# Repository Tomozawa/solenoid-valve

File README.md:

# solenoid-valve
[こちら](https://github.com/funi007/solenoid-valve.git)の電磁弁基板の改良版です。未テストですので使用に際しては十分注意してください。

# 履歴
## 改良基板の初版
- 2023/11/03
- ERC and DRC check
- 6f543627d558cafed8350256de44e78604443efa
- 改良基板の初期版。未テスト。

# 改良点
## フォトリレーが焼ける問題を解消
フォトリレーに負電圧がかかることで内部のFETが焼ける問題を解消しました。フォトリレー自体を採用せず、FETによるオープンドレイン出力としました。

## XT30コネクタに変更
駆動用電源のコネクタをEPコネクタからXT30コネクタ(オス)に変更しました。

## DCDCコンバータの安定性・効率を向上
DCDCコンバータに適正な負荷をかけ、連続モードでの動作とすることで、DCDCコンバータの安定性を改善ました。また、効率の上昇や高調波ノイズの低減も期待できます。

## フォトカプラへの配線を改善
ベタパターンの島ができにくいように、フォトカプラへの配線をまとめました。

# 問題点

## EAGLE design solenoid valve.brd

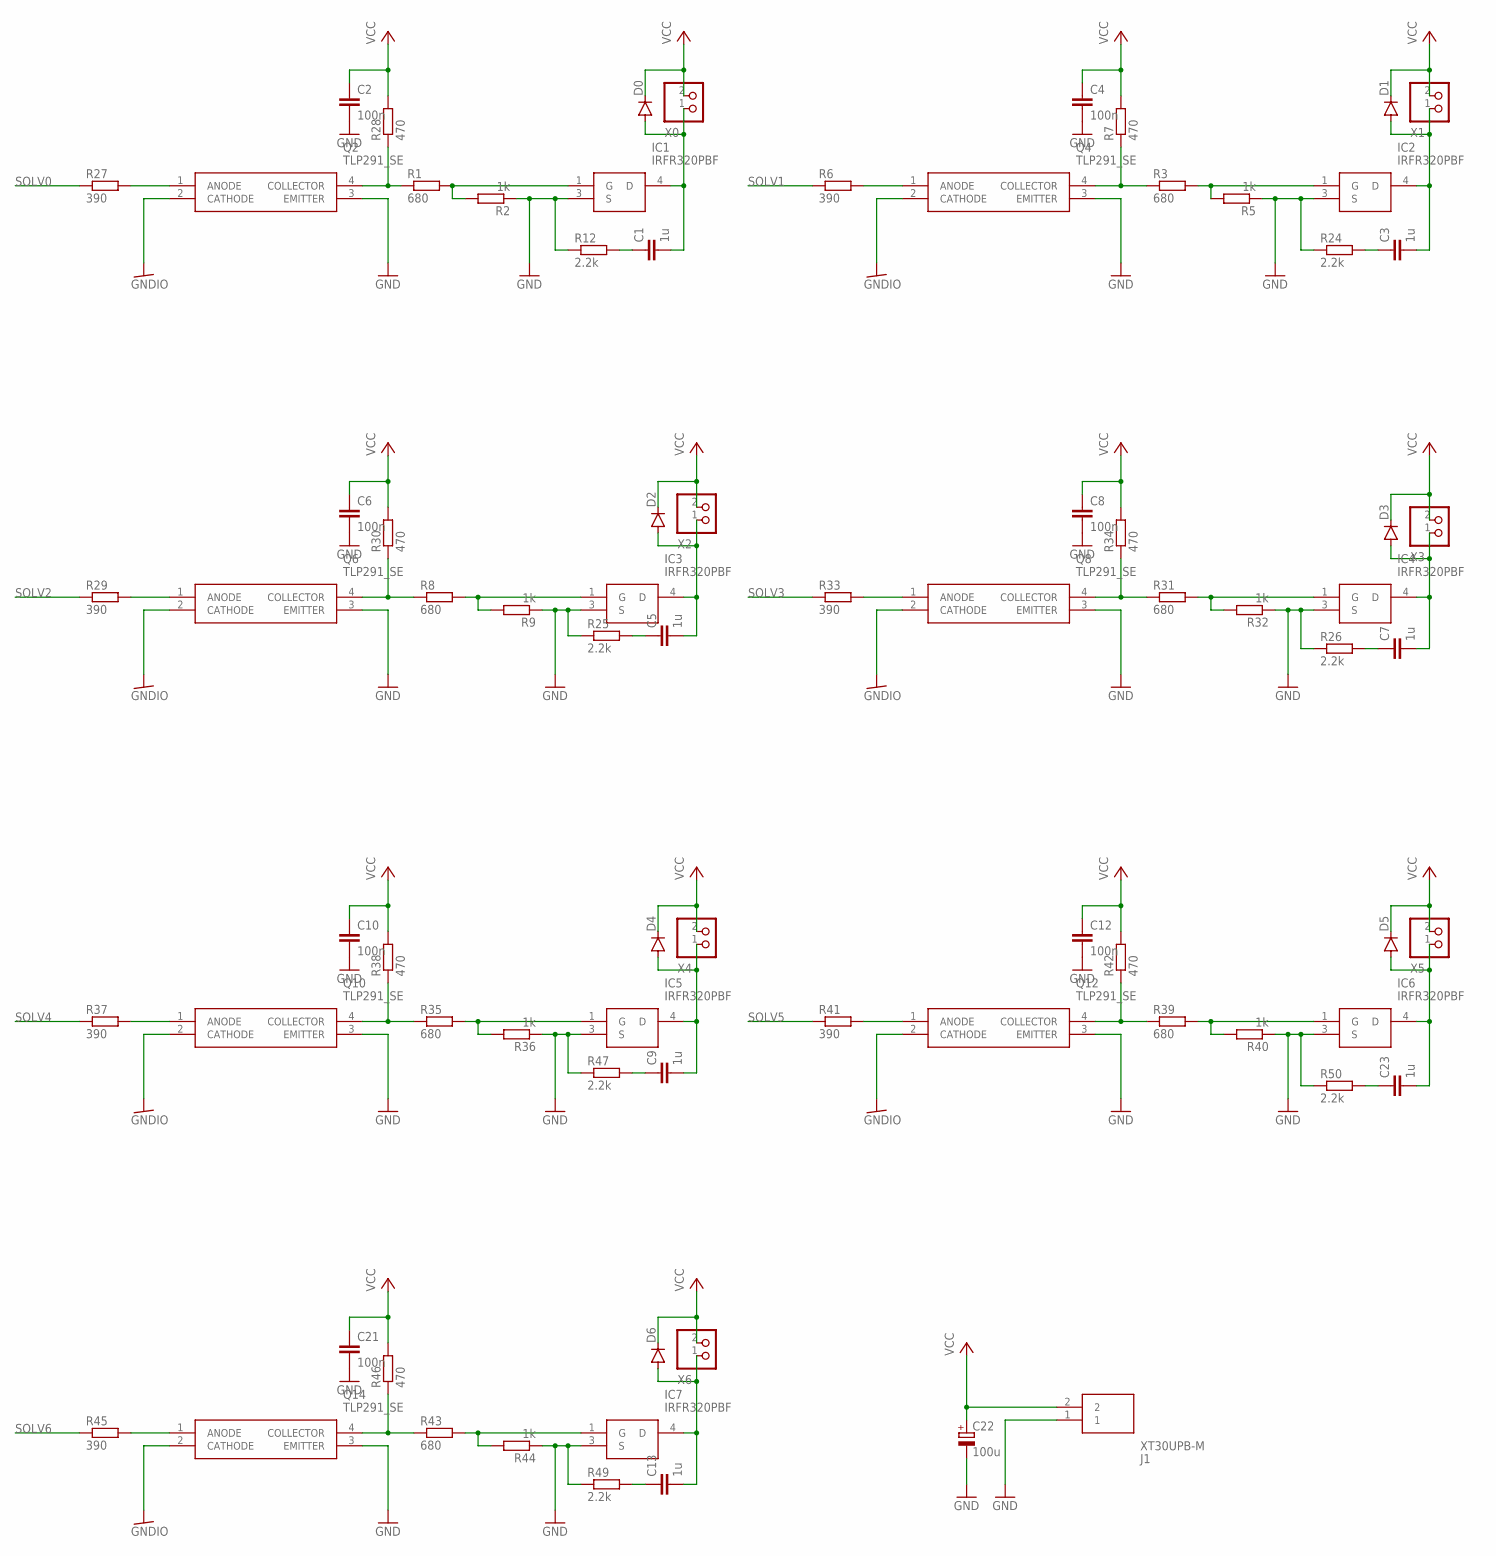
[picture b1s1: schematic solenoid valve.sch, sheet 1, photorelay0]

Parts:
C1, C3, C5, C7, C9, C13, C23: 1u; C0603
C2, C4, C6, C8, C10, C12, C21: 100n; C0603
C22: 100u; E2-5
D0, D1, D2, D3, D4, D5, D6: DIODE-SOD123; SOD123
IC1, IC2, IC3, IC4, IC5, IC6, IC7: IRFR320PBF; TO228P990X238-3N
J1: XT30UPB-M; SHDR2W160P0X500_1X2_1020X520X1
Q2, Q4, Q6, Q8, Q10, Q12, Q14: TLP291_SE; SOIC127P700X230-4N
R1, R3, R8, R31, R35, R39, R43: 680; R0603
R2, R5, R9, R32, R36, R40, R44: 1k; R0603
R6, R27, R29, R33, R37, R41, R45: 390; R0603
R7, R28, R30, R34, R38, R42, R46: 470; R0603
R12, R24, R25, R26, R47, R49, R50: 2.2k; R0603
X0, X1, X2, X3, X4, X5, X6: S2B-XASK-1

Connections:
GND: C2.2, C4.2, C6.2, C8.2, C10.2, C12.2, C21.2, C22.-, IC1.3 (S), IC2.3 (S), IC3.3 (S), IC4.3 (S), IC5.3 (S), IC6.3 (S), IC7.3 (S), J1.1, Q2.3 (EMITTER), Q4.3 (EMITTER), Q6.3 (EMITTER), Q8.3 (EMITTER), Q10.3 (EMITTER), Q12.3 (EMITTER), Q14.3 (EMITTER), R2.1, R5.1, R9.1, R12.1, R24.1, R25.1, R26.1, R32.1, R36.1, R40.1, R44.1, R47.1, R49.1, R50.1
GNDIO: Q2.2 (CATHODE), Q4.2 (CATHODE), Q6.2 (CATHODE), Q8.2 (CATHODE), Q10.2 (CATHODE), Q12.2 (CATHODE), Q14.2 (CATHODE); also elsewhere on the board
unnamed: IC2.1 (G), R3.2, R5.2
unnamed: C3.2, D1.A, IC2.4 (D), X1.1
unnamed: Q2.4 (COLLECTOR), R1.1, R28.1
unnamed: Q4.1 (ANODE), R6.2
unnamed: Q4.4 (COLLECTOR), R3.1, R7.1
unnamed: IC1.1 (G), R1.2, R2.2
unnamed: C1.2, D0.A, IC1.4 (D), X0.1
unnamed: IC3.1 (G), R8.2, R9.2
unnamed: Q2.1 (ANODE), R27.2
unnamed: C5.2, D2.A, IC3.4 (D), X2.1
unnamed: Q6.1 (ANODE), R29.2
unnamed: Q6.4 (COLLECTOR), R8.1, R30.1
unnamed: C7.2, D3.A, IC4.4 (D), X3.1
unnamed: C9.2, D4.A, IC5.4 (D), X4.1
unnamed: IC4.1 (G), R31.2, R32.2
unnamed: C3.1, R24.2
unnamed: C23.1, R50.2
unnamed: C23.2, D5.A, IC6.4 (D), X5.1
unnamed: C5.1, R25.2
unnamed: IC7.1 (G), R43.2, R44.2
unnamed: Q8.1 (ANODE), R33.2
unnamed: Q8.4 (COLLECTOR), R31.1, R34.1
unnamed: IC5.1 (G), R35.2, R36.2
unnamed: Q10.1 (ANODE), R37.2
unnamed: Q10.4 (COLLECTOR), R35.1, R38.1
unnamed: IC6.1 (G), R39.2, R40.2
unnamed: Q12.1 (ANODE), R41.2
unnamed: Q12.4 (COLLECTOR), R39.1, R42.1
unnamed: C13.2, D6.A, IC7.4 (D), X6.1
unnamed: Q14.1 (ANODE), R45.2
unnamed: Q14.4 (COLLECTOR), R43.1, R46.1
unnamed: C7.1, R26.2
unnamed: C9.1, R47.2
unnamed: C13.1, R49.2
unnamed: C1.1, R12.2
SOLV0: R27.1; also elsewhere on the board
SOLV1: R6.1; also elsewhere on the board
SOLV2: R29.1; also elsewhere on the board
SOLV3: R33.1; also elsewhere on the board
SOLV4: R37.1; also elsewhere on the board
SOLV5: R41.1; also elsewhere on the board
SOLV6: R45.1; also elsewhere on the board
VCC: C2.1, C4.1, C6.1, C8.1, C10.1, C12.1, C21.1, C22.+, D0.C, D1.C, D2.C, D3.C, D4.C, D5.C, D6.C, J1.2, R7.2, R28.2, R30.2, R34.2, R38.2, R42.2, R46.2, X0.2, X1.2, X2.2, X3.2, X4.2, X5.2, X6.2

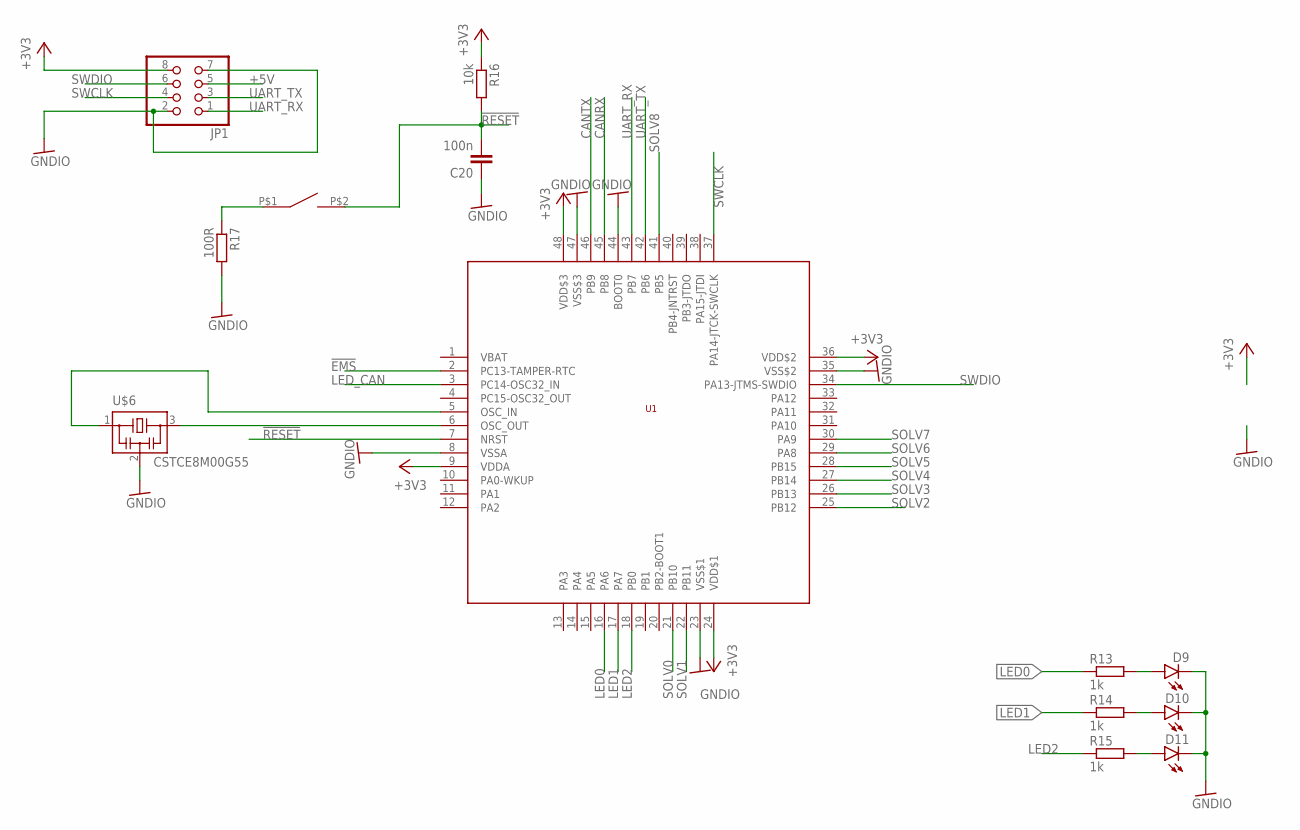
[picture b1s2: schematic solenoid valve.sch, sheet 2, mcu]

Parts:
C20: 100n; C0603
D9, D10, D11: LEDCHIPLED_0805; CHIPLED_0805
JP1: PINHD-2X4; 2X04
R13, R14, R15: 1k; R0603
R16: 10k; R0603
R17: 100R; R0603
SW1: SWITCH_TACTILETOP; SWITCH_TACTILE_3X6
U1: STM32F103C8; LQFP48
U$6: CSTCE8M00G55

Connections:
!EMS: U1.2 (PC13-TAMPER-RTC); also elsewhere on the board
!RESET: C20.2, R16.2, SW1.P$2 (2), U1.7 (NRST)
+3V3: JP1.8, R16.1, U1.9 (VDDA), U1.24 (VDD$1), U1.36 (VDD$2), U1.48 (VDD$3); also elsewhere on the board
+5V: JP1.5; also elsewhere on the board
CANRX: U1.45 (PB8); also elsewhere on the board
CANTX: U1.46 (PB9); also elsewhere on the board
GNDIO: C20.1, D9.C, D10.C, D11.C, JP1.2, JP1.7, R17.2, U1.8 (VSSA), U1.23 (VSS$1), U1.35 (VSS$2), U1.44 (BOOT0), U1.47 (VSS$3), U$6.2; also elsewhere on the board
LED0: R13.1, U1.16 (PA6)
LED1: R14.1, U1.17 (PA7)
LED2: R15.1, U1.18 (PB0)
LED_CAN: U1.3 (PC14-OSC32_IN); also elsewhere on the board
unnamed: D10.A, R14.2
unnamed: D9.A, R13.2
unnamed: U1.6 (OSC_OUT), U$6.3
unnamed: R17.1, SW1.P$1 (1)
unnamed: U1.5 (OSC_IN), U$6.1
unnamed: D11.A, R15.2
SOLV0: U1.21 (PB10); also elsewhere on the board
SOLV1: U1.22 (PB11); also elsewhere on the board
SOLV2: U1.25 (PB12); also elsewhere on the board
SOLV3: U1.26 (PB13); also elsewhere on the board
SOLV4: U1.27 (PB14); also elsewhere on the board
SOLV5: U1.28 (PB15); also elsewhere on the board
SOLV6: U1.29 (PA8); also elsewhere on the board
SOLV7: U1.30 (PA9)
SOLV8: U1.41 (PB5)
SWCLK: JP1.4, U1.37 (PA14-JTCK-SWCLK)
SWDIO: JP1.6, U1.34 (PA13-JTMS-SWDIO)
UART_RX: JP1.1, U1.43 (PB7)
UART_TX: JP1.3, U1.42 (PB6)

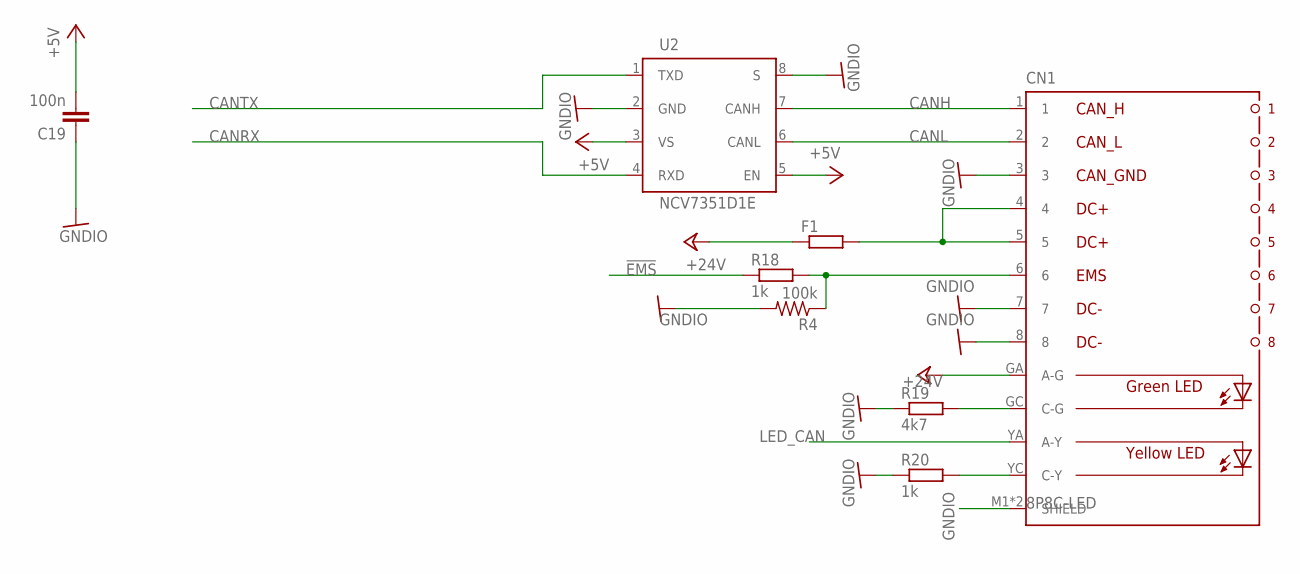
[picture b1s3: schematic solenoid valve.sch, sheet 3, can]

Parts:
C19: 100n; C0603
CN1: 8P8C-LED
F1: R-EU_R1206; R1206
R4: 100k; R0603
R18, R20: 1k; R0603
R19: 4k7; R0603
U2: NCV7351D1E; SO08

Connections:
!EMS: R18.1; also elsewhere on the board
+5V: C19.2, U2.3 (VS), U2.5 (EN); also elsewhere on the board
+24V: CN1.GA (A-G), F1.1; also elsewhere on the board
CANH: CN1.1, U2.7 (CANH)
CANL: CN1.2, U2.6 (CANL)
CANRX: U2.4 (RXD); also elsewhere on the board
CANTX: U2.1 (TXD); also elsewhere on the board
GNDIO: C19.1, CN1.3, CN1.7, CN1.8, CN1.M1 (SHIELD), CN1.M2 (SHIELD), R4.2, R19.1, R20.1, U2.2 (GND), U2.8 (S); also elsewhere on the board
LED_CAN: CN1.YA (A-Y); also elsewhere on the board
unnamed: CN1.4, CN1.5, F1.2
unnamed: CN1.YC (C-Y), R20.2
unnamed: CN1.GC (C-G), R19.2
unnamed: CN1.6, R4.1, R18.2

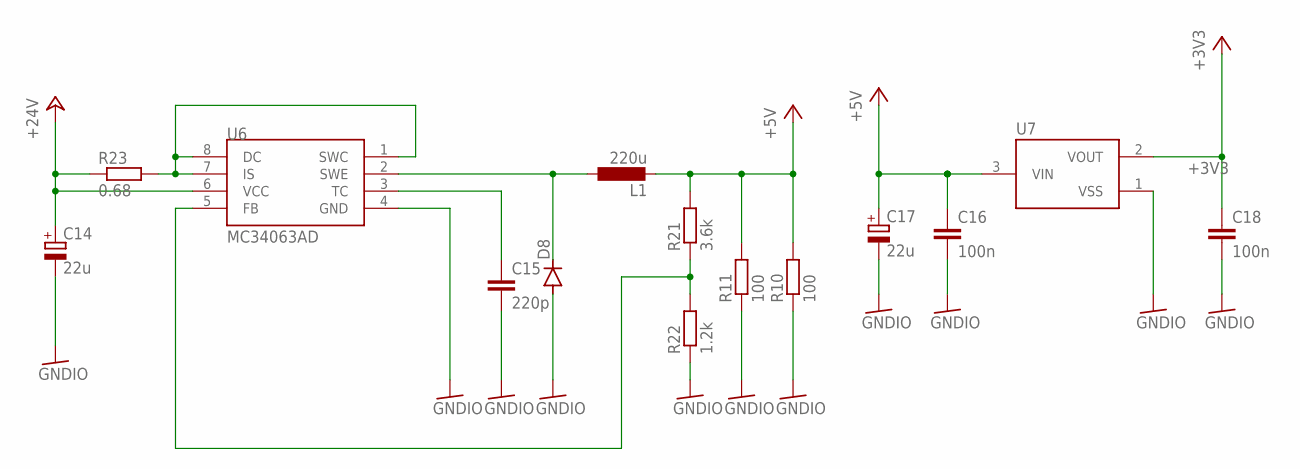
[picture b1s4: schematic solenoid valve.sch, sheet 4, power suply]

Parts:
C14, C17: 22u; E2-5
C15: 220p; C0603
C16, C18: 100n; C0603
D8: DIODE-SOD123; SOD123
L1: 220u; L5852
R10, R11: 100; R0603
R21: 3.6k; R0603
R22: 1.2k; R0603
R23: 0.68; R1206
U6: MC34063AD; SOIC8
U7: XC6206; SOT95P240X110-3

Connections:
+3V3: C18.1, U7.2 (VOUT); also elsewhere on the board
+5V: C16.1, C17.+, L1.P$2 (2), R10.2, R11.2, R21.2, U7.3 (VIN); also elsewhere on the board
+24V: C14.+, R23.1, U6.6 (VCC); also elsewhere on the board
GNDIO: C14.-, C15.2, C16.2, C17.-, C18.2, D8.A, R10.1, R11.1, R22.1, U6.4 (GND), U7.1 (VSS); also elsewhere on the board
unnamed: R23.2, U6.1 (SWC), U6.7 (IS), U6.8 (DC)
unnamed: D8.C, L1.P$1 (1), U6.2 (SWE)
unnamed: C15.1, U6.3 (TC)
unnamed: R21.1, R22.2, U6.5 (FB)

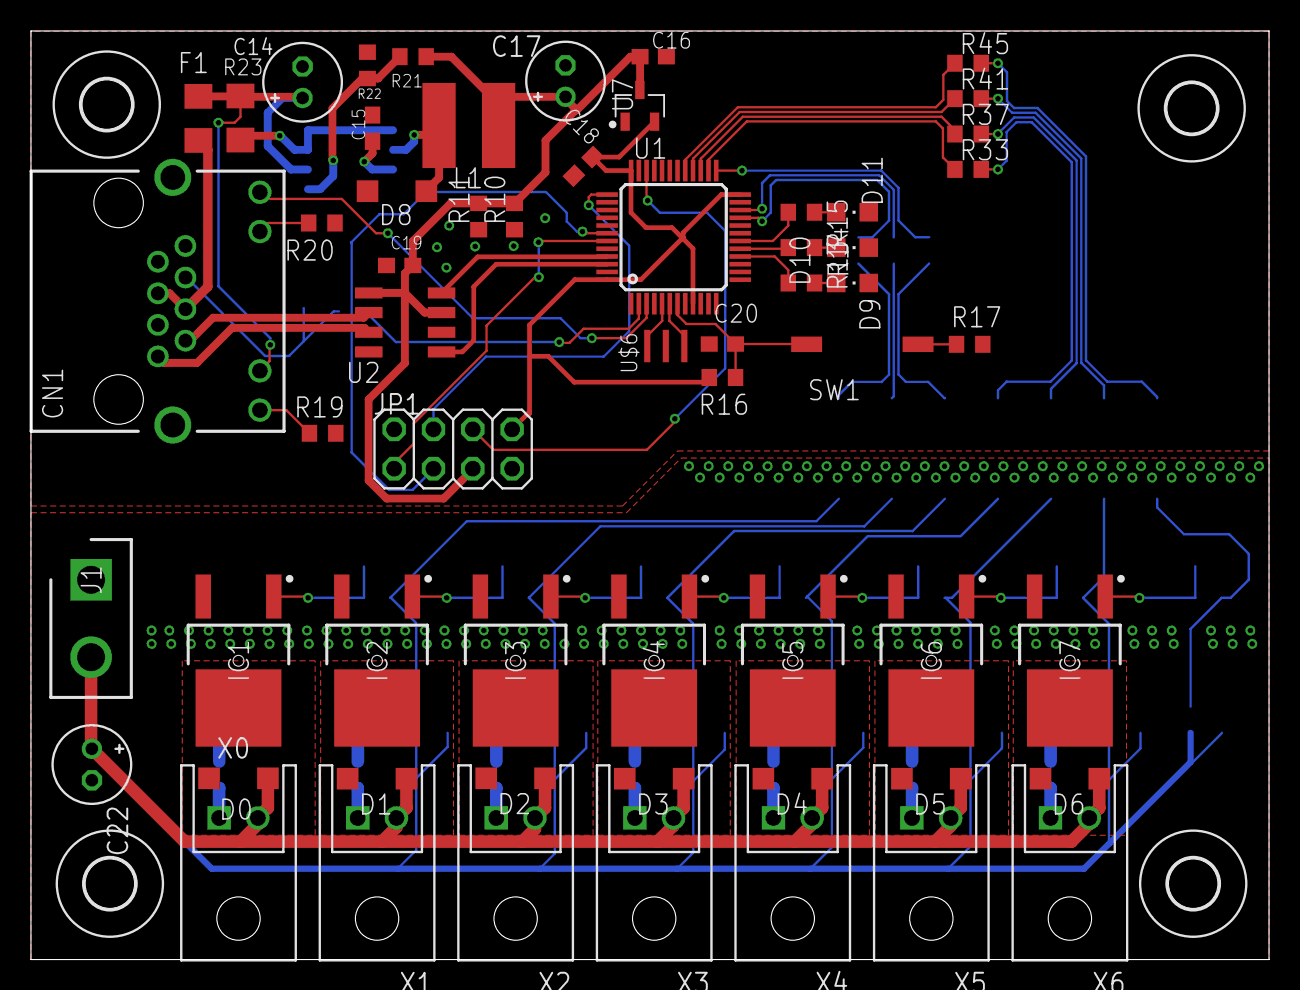
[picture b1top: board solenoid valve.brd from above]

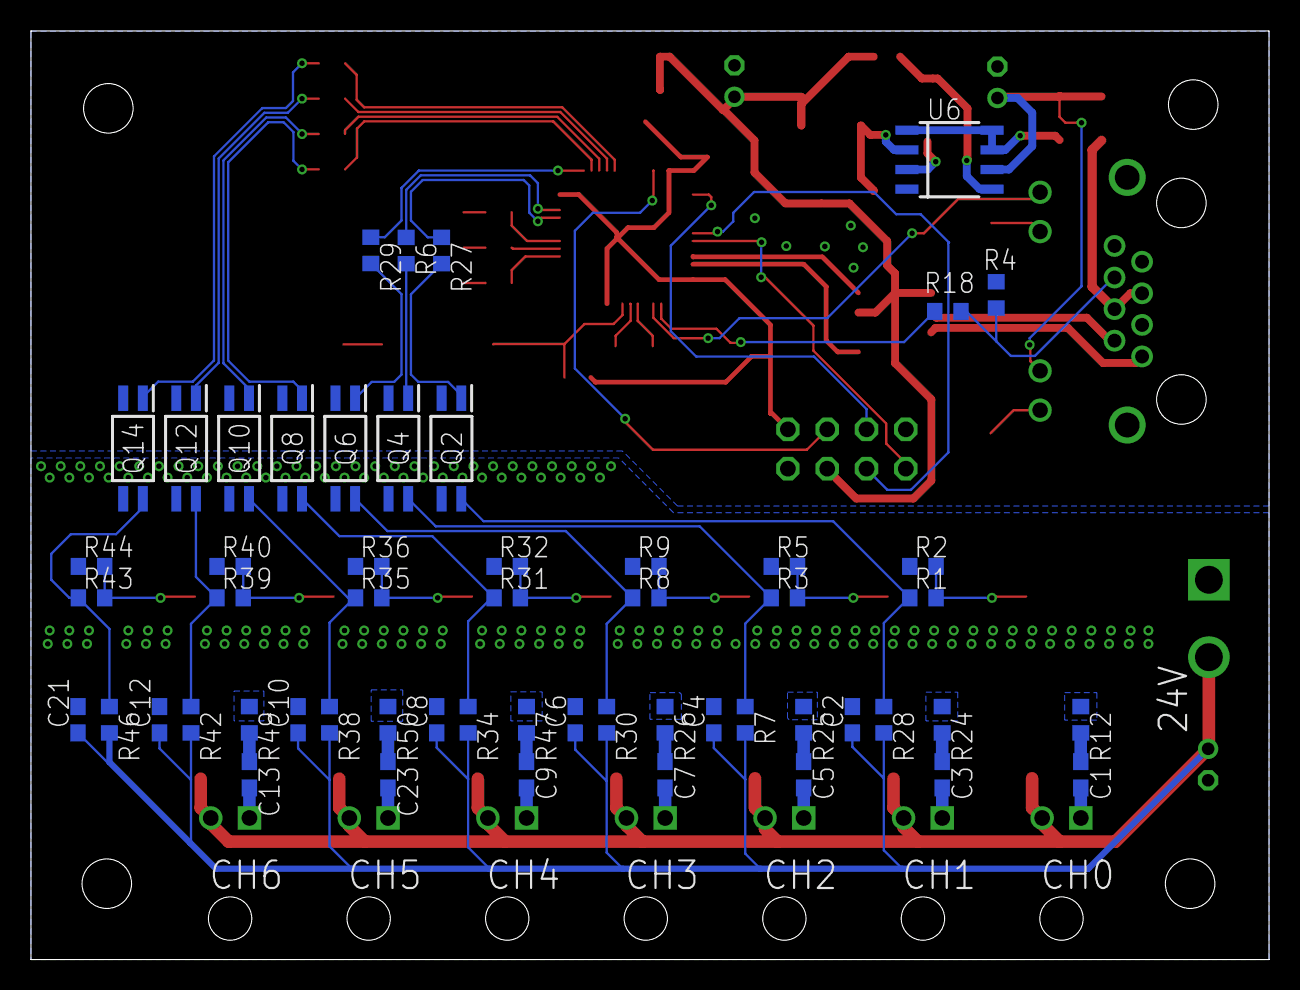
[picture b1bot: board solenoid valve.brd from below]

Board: 2 copper layers, 80.0 x 60.0 mm, 118 parts (55 on the bottom side), 76 nets.

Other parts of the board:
U$1, U$2, U$3, U$4: 3,2

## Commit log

2023-11-03 Anti Reverse Volatge
2023-11-03 Anti Reverse Voltage
2023-11-03 ERC and DRC check
